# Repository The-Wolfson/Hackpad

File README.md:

# MIDI (Pro) Pad
A hackpad built for [Hacklub's YSWS](hackpad.hackclub.com) that sends MIDI Control Messages to your DAW of choice. It features 2 rotary encoders, 9 switches, and 16 addressable LEDs.

## BOM
| Part | Quantity |
| - | - |
| XIAO RP2040 | 1 |
| EC11 Rotary Encoder | 2 |
| SK6812 MINI-E | 16 |
| MX-Style Switch | 7|
| Through-hole 1N4148 Diode | 9 |
| M3x16mm Screw | 4 |
| M3x5mx4mm Heatset Insert | 4 |

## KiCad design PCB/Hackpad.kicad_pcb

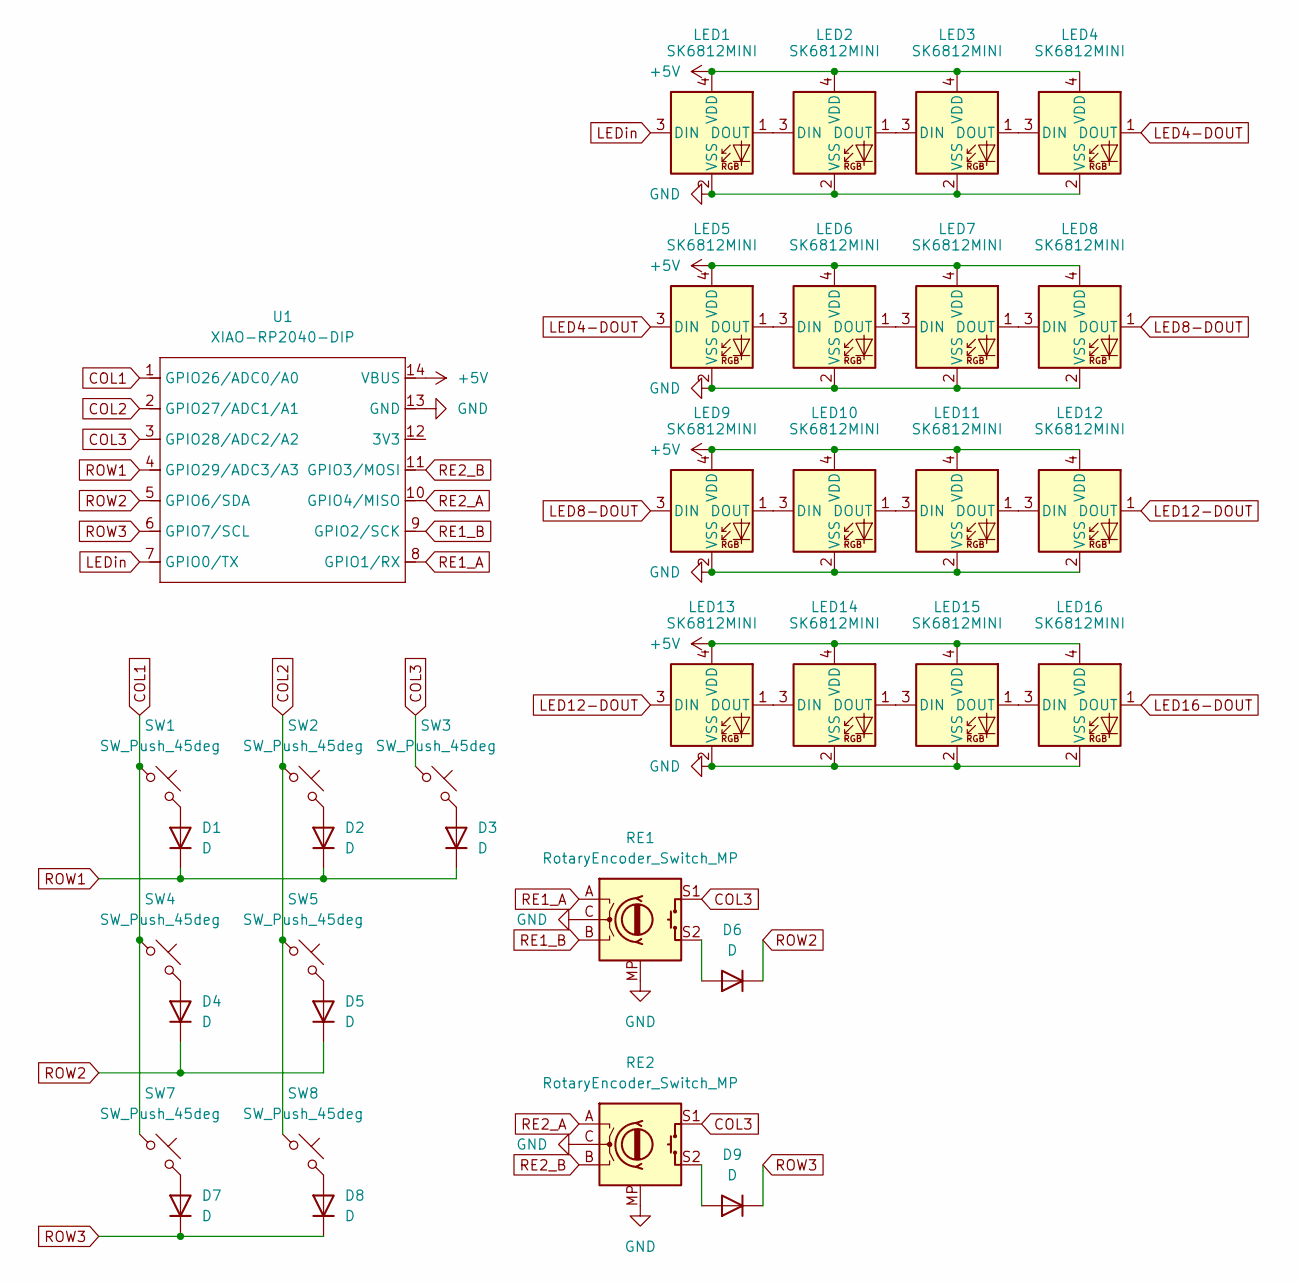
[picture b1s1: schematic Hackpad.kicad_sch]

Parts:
D1, D2, D3, D4, D5, D6, D7, D8, D9: D; D_DO-35_SOD27_P7.62mm_Horizontal
LED1, LED2, LED3, LED4, LED5, LED6, LED7, LED8, LED9, LED10, LED11, LED12, LED13, LED14, LED15, LED16: SK6812MINI; SK6812-MINI-E
RE1, RE2: RotaryEncoder_Switch_MP; RotaryEncoder_Alps_EC11E-Switch_Vertical_H20mm
SW1, SW2, SW3, SW4, SW5, SW7, SW8: SW_Push_45deg; SW_Cherry_MX_1.00u_PCB
U1: XIAO-RP2040-DIP

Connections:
+5V: LED1.4 (VDD), LED2.4 (VDD), LED3.4 (VDD), LED4.4 (VDD), LED5.4 (VDD), LED6.4 (VDD), LED7.4 (VDD), LED8.4 (VDD), LED9.4 (VDD), LED10.4 (VDD), LED11.4 (VDD), LED12.4 (VDD), LED13.4 (VDD), LED14.4 (VDD), LED15.4 (VDD), LED16.4 (VDD), U1.14 (VBUS)
COL1: SW1.1, SW4.1, SW7.1, U1.1 (GPIO26/ADC0/A0)
COL2: SW2.1, SW5.1, SW8.1, U1.2 (GPIO27/ADC1/A1)
COL3: RE1.S1, RE2.S1, SW3.1, U1.3 (GPIO28/ADC2/A2)
GND: LED1.2 (VSS), LED2.2 (VSS), LED3.2 (VSS), LED4.2 (VSS), LED5.2 (VSS), LED6.2 (VSS), LED7.2 (VSS), LED8.2 (VSS), LED9.2 (VSS), LED10.2 (VSS), LED11.2 (VSS), LED12.2 (VSS), LED13.2 (VSS), LED14.2 (VSS), LED15.2 (VSS), LED16.2 (VSS), RE1.C, RE1.MP, RE2.C, RE2.MP, U1.13 (GND)
LED4-DOUT: LED4.1 (DOUT), LED5.3 (DIN)
LED8-DOUT: LED8.1 (DOUT), LED9.3 (DIN)
LED12-DOUT: LED12.1 (DOUT), LED13.3 (DIN)
LED16-DOUT: LED16.1 (DOUT)
LEDin: LED1.3 (DIN), U1.7 (GPIO0/TX)
unnamed: D1.2 (A), SW1.2
unnamed: D2.2 (A), SW2.2
unnamed: D3.2 (A), SW3.2
unnamed: D4.2 (A), SW4.2
unnamed: D5.2 (A), SW5.2
unnamed: D6.2 (A), RE1.S2
unnamed: D7.2 (A), SW7.2
unnamed: D8.2 (A), SW8.2
unnamed: D9.2 (A), RE2.S2
unnamed: LED1.1 (DOUT), LED2.3 (DIN)
unnamed: LED2.1 (DOUT), LED3.3 (DIN)
unnamed: LED3.1 (DOUT), LED4.3 (DIN)
unnamed: LED5.1 (DOUT), LED6.3 (DIN)
unnamed: LED6.1 (DOUT), LED7.3 (DIN)
unnamed: LED7.1 (DOUT), LED8.3 (DIN)
unnamed: LED9.1 (DOUT), LED10.3 (DIN)
unnamed: LED10.1 (DOUT), LED11.3 (DIN)
unnamed: LED11.1 (DOUT), LED12.3 (DIN)
unnamed: LED13.1 (DOUT), LED14.3 (DIN)
unnamed: LED14.1 (DOUT), LED15.3 (DIN)
unnamed: LED15.1 (DOUT), LED16.3 (DIN)
RE1_A: RE1.A, U1.8 (GPIO1/RX)
RE1_B: RE1.B, U1.9 (GPIO2/SCK)
RE2_A: RE2.A, U1.10 (GPIO4/MISO)
RE2_B: RE2.B, U1.11 (GPIO3/MOSI)
ROW1: D1.1 (K), D2.1 (K), D3.1 (K), U1.4 (GPIO29/ADC3/A3)
ROW2: D4.1 (K), D5.1 (K), D6.1 (K), U1.5 (GPIO6/SDA)
ROW3: D7.1 (K), D8.1 (K), D9.1 (K), U1.6 (GPIO7/SCL)

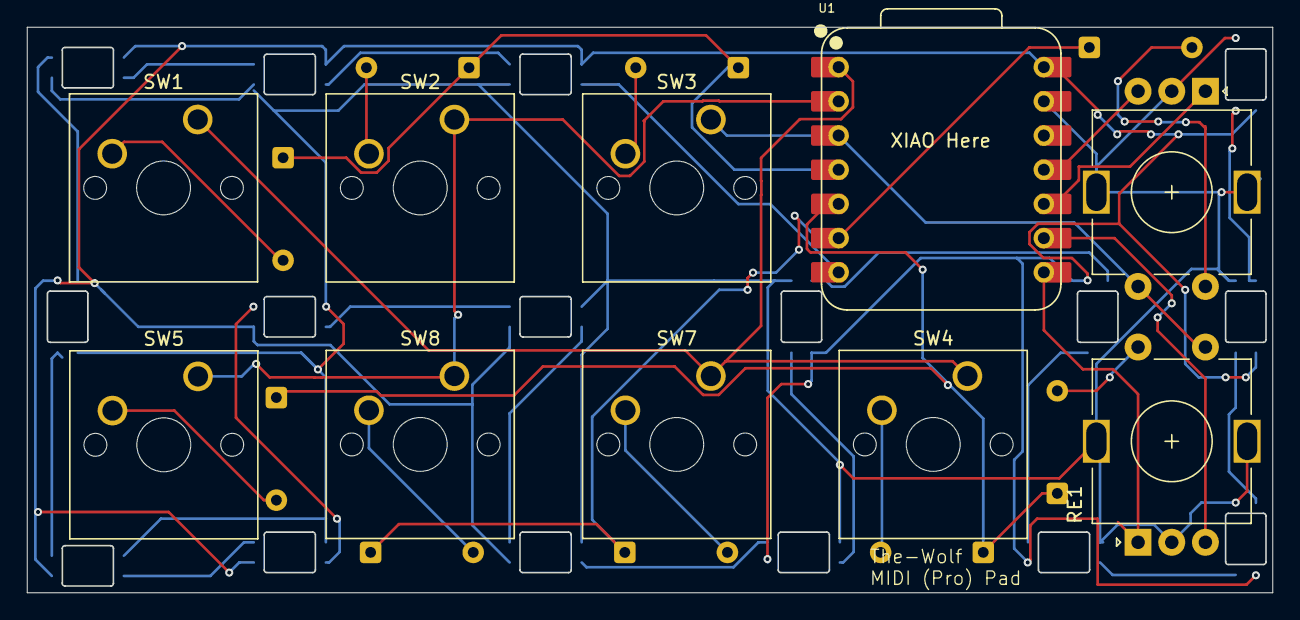
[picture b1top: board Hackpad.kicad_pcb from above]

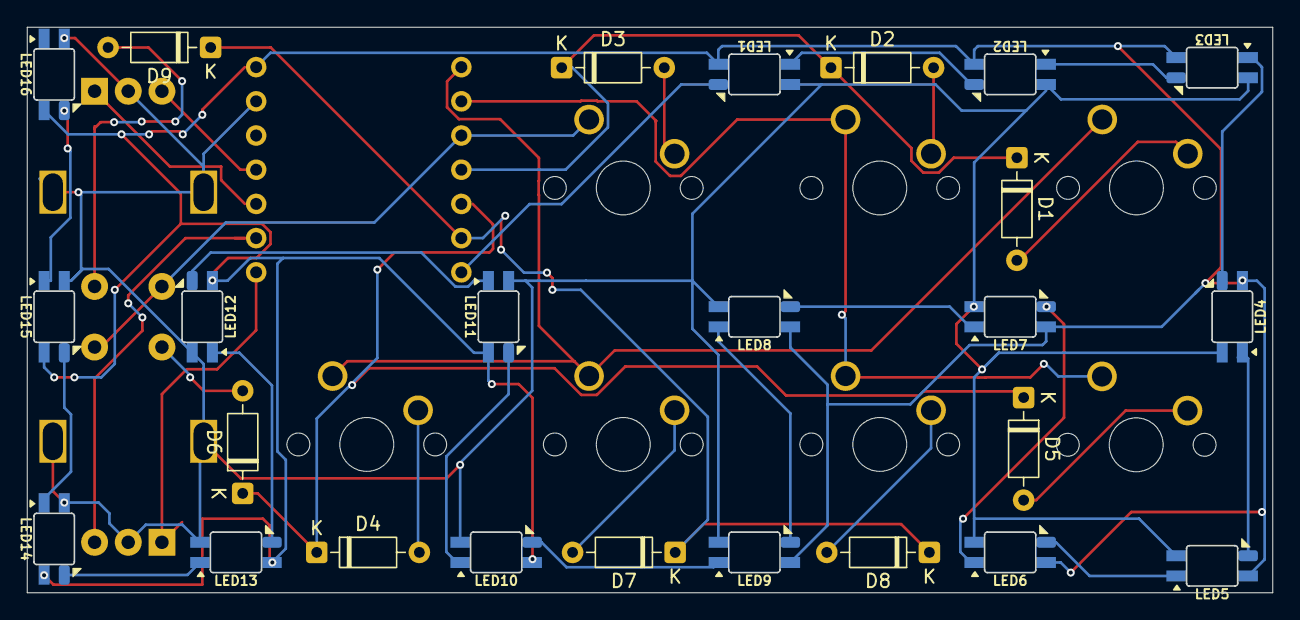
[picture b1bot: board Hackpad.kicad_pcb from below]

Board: 2 copper layers, 92.4 x 41.9 mm, 35 parts (25 on the bottom side), 37 nets.

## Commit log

2025-07-17 Added README.md
2025-07-17 added text
